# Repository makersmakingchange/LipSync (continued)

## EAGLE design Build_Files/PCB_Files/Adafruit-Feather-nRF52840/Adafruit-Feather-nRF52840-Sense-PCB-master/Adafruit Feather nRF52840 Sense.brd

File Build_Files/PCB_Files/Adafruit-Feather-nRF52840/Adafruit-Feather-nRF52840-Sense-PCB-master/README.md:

## Adafruit Feather nRF52840 Sense PCB

<a href="http://www.adafruit.com/products/4516"><br/>
Click here to purchase one from the Adafruit shop</a>

PCB files for the Adafruit Feather nRF52840 Sense. 

Format is EagleCAD schematic and board layout
* https://www.adafruit.com/product/4516

### Description

The Adafruit Feather Bluefruit Sense takes our popular Feather nRF52840 Express and adds a smorgasbord of sensors to make a great wireless sensor platform. This Feather microcontroller comes with Bluetooth Low Energy and native USB support featuring the nRF52840!  This Feather is an 'all-in-one' Arduino-compatible + Bluetooth Low Energy with built in USB plus battery charging. With native USB it works great with CircuitPython, too.

Like the Feather nRF52840, this chip comes with Arduino IDE support - you can program the nRF52840 chip directly to take full advantage of the Cortex-M4 processor, and then calling into the Nordic SoftDevice radio stack when you need to communicate over BLE. Since the underlying API and peripherals are the same for the '832 and '840, you can supercharge your older nRF52832 projects with the same exact code, with a single recompile!

This Feather is also a BLE-friendly CircuitPython board! CircuitPython works best with disk drive access, and this is the only BLE-plus-USB-native chip that has the memory to handle running a little Python interpreter. The massive RAM and speedy Cortex M4F chip make this a good match. Make centrals or peripherals with the ease of CircuitPython.

A chorus of supporting sensors surround the module so you can do all sorts of environmental and motion sensing:

* ST Micro series 9-DoF motion - LSM6DS33 Accel/Gyro + LIS3MDL magnetometer
* APDS9960 Proximity, Light, Color, and Gesture Sensor
* PDM Microphone sound sensor
* SHT Humidity
* BMP280 temperature and barometric pressure/altitude

Features:

* ARM Cortex M4F (with HW floating point acceleration) running at 64MHz
* 1MB flash and 256KB SRAM
* Native Open Source USB stack - pre-programmed with UF2 bootloader
* Bluetooth Low Energy compatible 2.4GHz radio (Details available in the nRF52840 product specification)
* FCC / IC / TELEC certified module
* Up to +8dBm output power
* 21 GPIO, 6 x 12-bit ADC pins, up to 12 PWM outputs (3 PWM modules with 4 outputs each)
* Pin #13 red LED for general purpose blinking, Blue LED for general purpose connection status, NeoPixel for colorful feedback
* Power/enable pin
* Measures 2.0" x 0.9" x 0.28" (51mm x 23mm x 7.2mm) without headers soldered in
* Light as a (large?) feather - 6 grams
* 4 mounting holes
* Reset button
* SWD debug pads on bottom of PCB
* Works out of the box with all of our Adafruit FeatherWings! (Even the UART-using ones like the GPS FeatherWing)

### License

Adafruit invests time and resources providing this open source design, please support Adafruit and open-source hardware by purchasing products from [Adafruit](https://www.adafruit.com)!

Designed by Limor Fried/Ladyada for Adafruit Industries.

Creative Commons Attribution/Share-Alike, all text above must be included in any redistribution. 
See license.txt for additional details.

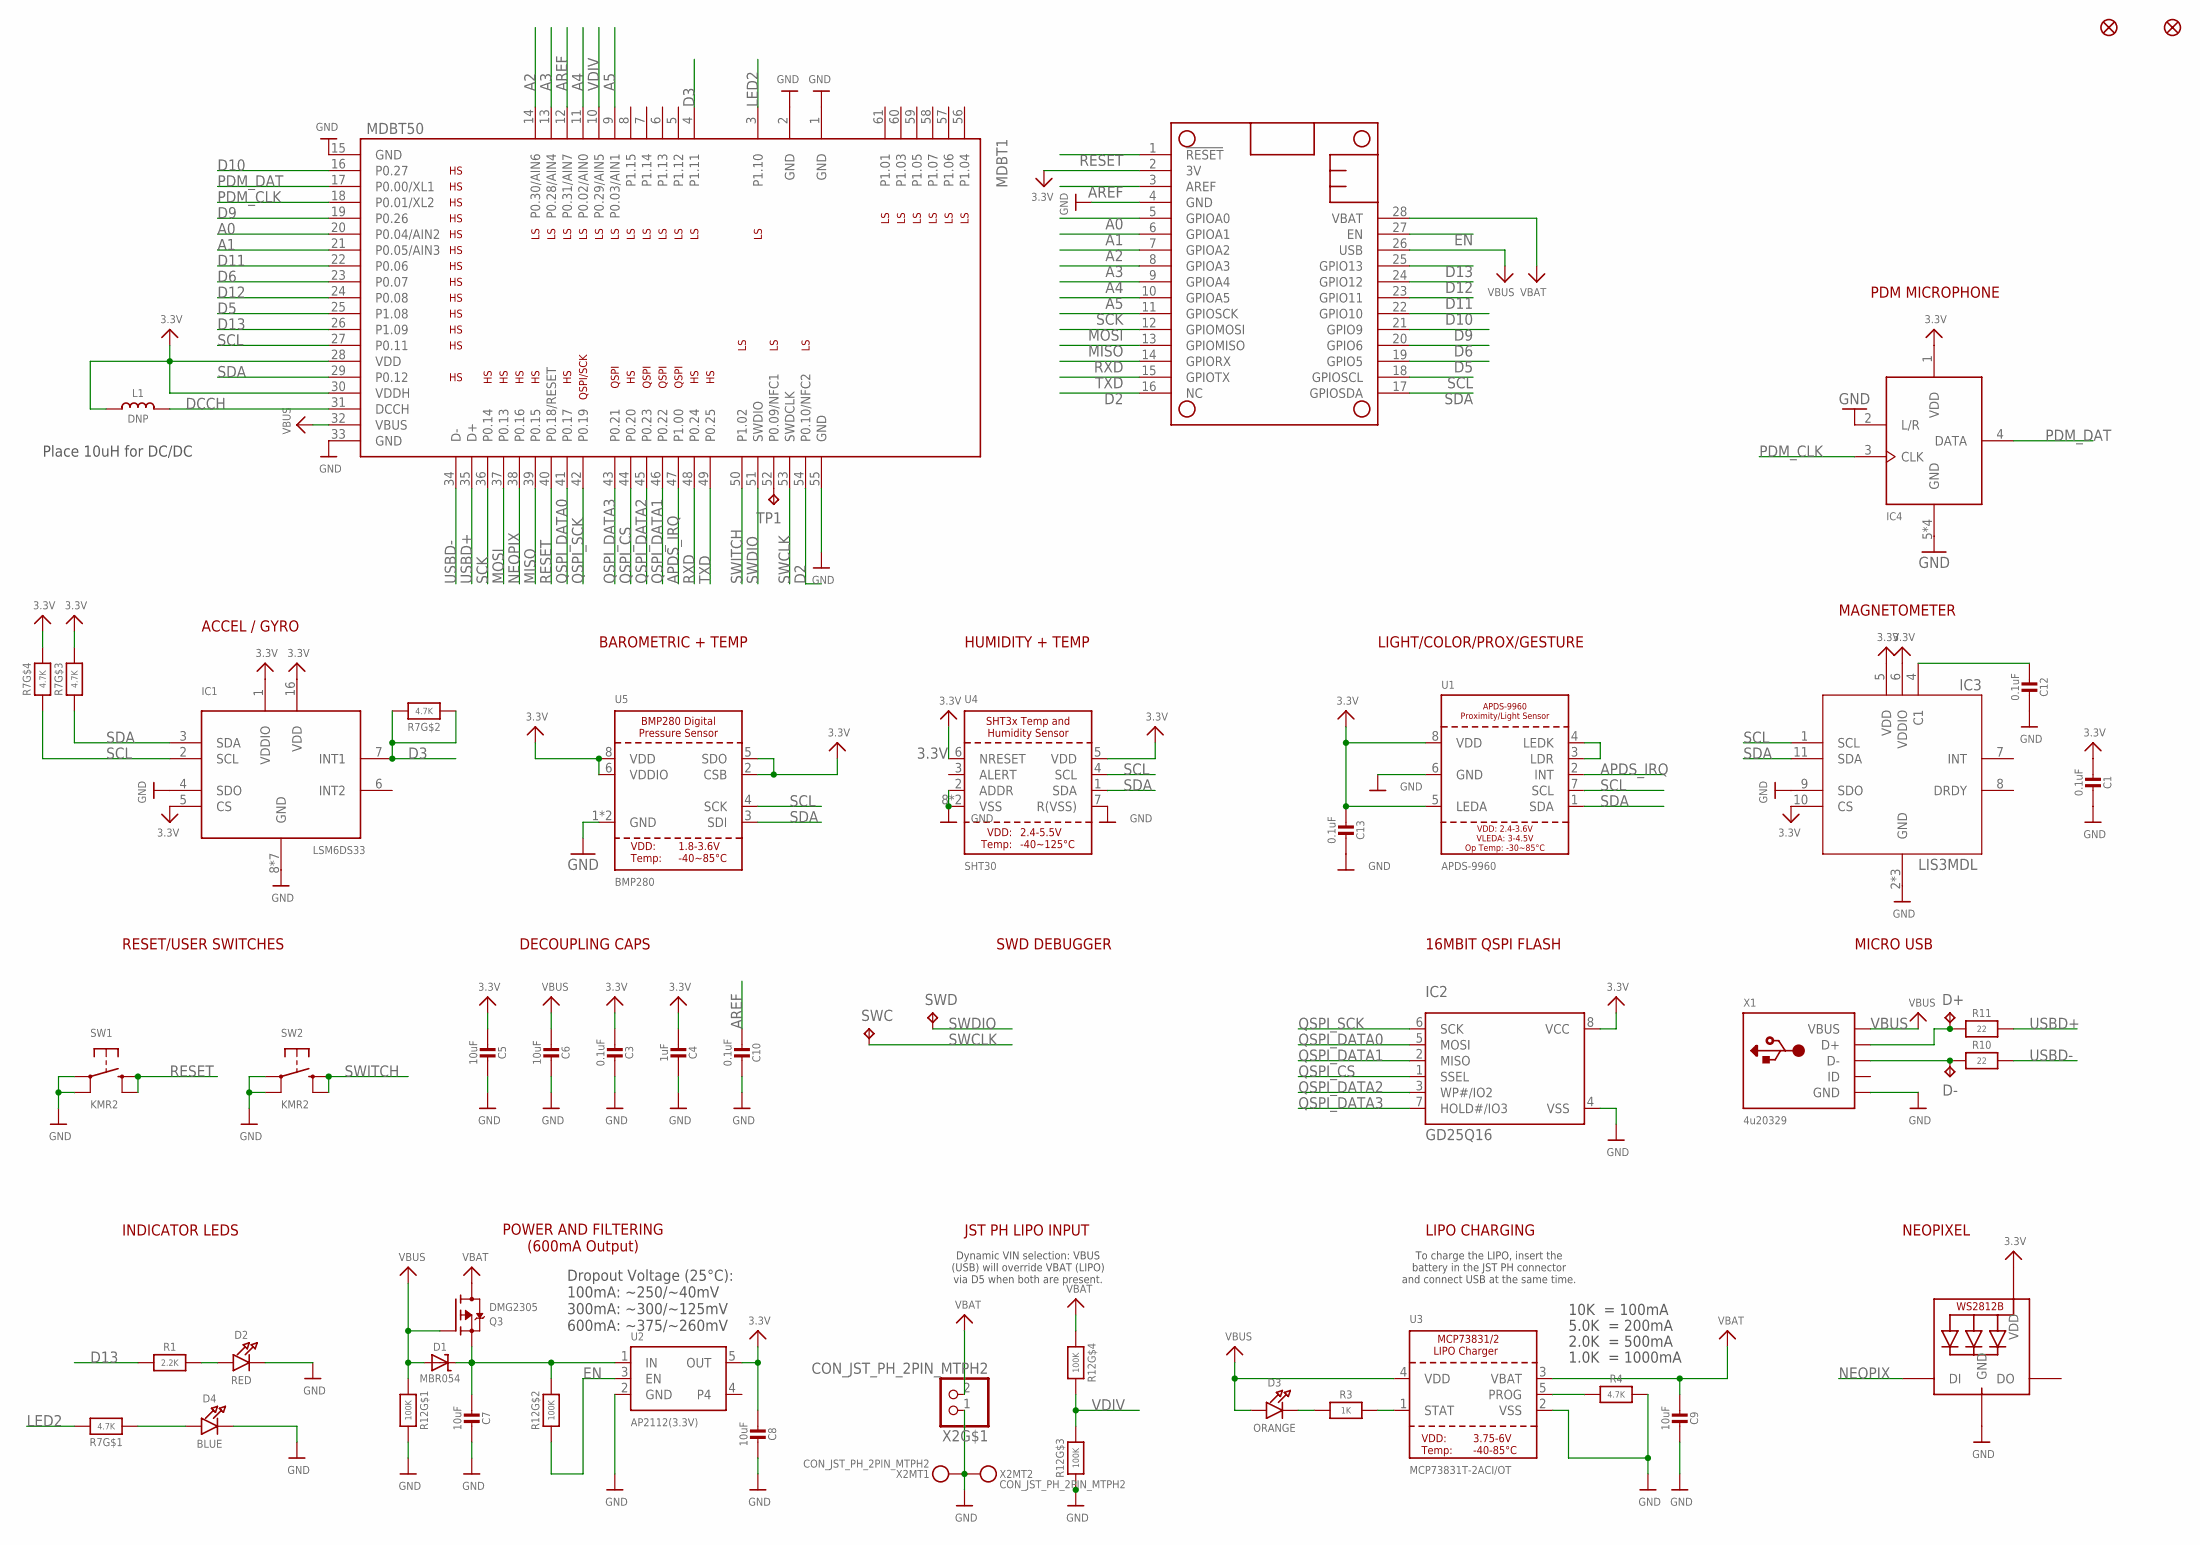
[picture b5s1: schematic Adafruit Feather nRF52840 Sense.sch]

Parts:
C1, C3, C10, C12, C13: 0.1uF; 0603-NO
C4: 1uF; 0603-NO
C5, C6, C7, C8, C9: 10uF; 0805-NO
D1: MBR054; SOD-123
D2: RED; CHIPLED_0805_NOOUTLINE
D3: ORANGE; CHIPLED_0805_NOOUTLINE
D4: BLUE; CHIPLED_0603_NOOUTLINE
D+: TPTP10R; TP10R
D-: TPTP10R; TP10R
FID1, FID2: FIDUCIAL_1MM
IC1: LSM6DS33; LGA16_3X3MM
IC2: GD25Q16; USON8
IC3: LIS3MDL; LGA12_2X2MM
IC4: MIC_PDM; SPK0415HM4H
L1: DNP; _0805MP
LED1: WS2812B3535; LED3535
MDBT1: MDBT50
MS1: FEATHERWING_NODIM
Q3: DMG2305; SOT23-R
R1: 2.2K; 0603-NO
R3: 1K; 0603-NO
R4: 4.7K; 0603-NO
R7: 4.7K; RESPACK_4X0603
R10, R11: 22; 0603-NO
R12: 100K; RESPACK_4X0603
SW1, SW2: KMR2; BTN_KMR2_4.6X2.8
SWC: TPTP12R; TP12R
SWD: TPTP12R; TP12R
TP1: TPTP10R; TP10R
U1: APDS-9960
U2: AP2112(3.3V); SOT23-5
U3: MCP73831T-2ACI/OT; SOT23-5
U4: SHT30; SHT3X
U5: BMP280
X1: 4u20329; 4UCONN_20329_V2
X2: CON_JST_PH_2PIN_MTPH2; JSTPH2

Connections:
3.3V: C1.2, C3.2, C4.2, C5.2, C8.2, C13.2, IC1.1 (VDDIO), IC1.5 (CS), IC1.16 (VDD), IC2.8 (VCC), IC3.5 (VDD), IC3.6 (VDDIO), IC3.10 (CS), IC4.1 (VDD), L1.1, LED1.2 (VDD), MDBT1.28 (VDD), MDBT1.30 (VDDH), MS1.2 (3V), R7.5 (2), R7.6 (2), U1.5 (LEDA), U1.8 (VDD), U2.5 (OUT), U4.5 (VDD), U4.6 (NRESET), U5.2 (CSB), U5.5 (SDO), U5.6 (VDDIO), U5.8 (VDD)
A0: MDBT1.20 (P0.04/AIN2), MS1.5 (GPIOA0)
A1: MDBT1.21 (P0.05/AIN3), MS1.6 (GPIOA1)
A2: MDBT1.14 (P0.30/AIN6), MS1.7 (GPIOA2)
A3: MDBT1.13 (P0.28/AIN4), MS1.8 (GPIOA3)
A4: MDBT1.11 (P0.02/AIN0), MS1.9 (GPIOA4)
A5: MDBT1.9 (P0.03/AIN1), MS1.10 (GPIOA5)
APDS_IRQ: MDBT1.47 (P1.00), U1.2 (INT)
AREF: C10.2, MDBT1.12 (P0.31/AIN7), MS1.3 (AREF)
CAP1: C12.2, IC3.4 (C1)
D2: MDBT1.54 (P0.10/NFC2), MS1.16 (NC)
D3: IC1.7 (INT1), MDBT1.4 (P1.11), R7.2 (1), R7.7 (2)
D5: MDBT1.25 (P1.08), MS1.19 (GPIO5)
D6: MDBT1.23 (P0.07), MS1.20 (GPIO6)
D9: MDBT1.19 (P0.26), MS1.21 (GPIO9)
D10: MDBT1.16 (P0.27), MS1.22 (GPIO10)
D11: MDBT1.22 (P0.06), MS1.23 (GPIO11)
D12: MDBT1.24 (P0.08), MS1.24 (GPIO12)
D13: MDBT1.26 (P1.09), MS1.25 (GPIO13), R1.1
D+: D+.TP, R11.1, X1.D+
D-: D-.TP, R10.1, X1.D-
DCCH: L1.2, MDBT1.31 (DCCH)
EN: MS1.27 (EN), R12.2 (1), U2.3 (EN)
GND: C1.1, C3.1, C4.1, C5.1, C6.1, C7.1, C8.1, C9.1, C10.1, C12.1, C13.1, D2.C, D4.C, IC1.4 (SDO), IC1.8 (GND), IC1.9 (GND), IC1.10 (GND), IC1.11 (GND), IC1.12 (GND), IC1.13 (GND), IC1.15 (GND), IC2.4 (VSS), IC3.2 (GND), IC3.3 (GND), IC3.9 (SDO), IC3.12 (GND), IC4.2 (L/R), IC4.5 (GND), IC4.6 (GND), IC4.7 (GND), IC4.8 (GND), LED1.4 (GND), MDBT1.1 (GND), MDBT1.2 (GND), MDBT1.15 (GND), MDBT1.33 (GND), MDBT1.55 (GND), MS1.4 (GND), R4.2, R12.3 (1), R12.8 (2), SW1.A, SW1.A' (P1), SW2.A, SW2.A' (P1), U1.6 (GND), U2.2 (GND), U3.2 (VSS), U4.2 (ADDR), U4.7 (R(VSS)), U4.8 (VSS), U4.THERMAL (VSS), U5.1 (GND), U5.7 (GND), X1.BASE@1 (GND), X1.BASE@2 (GND), X1.GND, X1.SPRT@1 (GND), X1.SPRT@2 (GND), X1.SPRT@3 (GND), X1.SPRT@4 (GND), X2.1, X2.NC1, X2.NC2
LED2: MDBT1.3 (P1.10), R7.8 (2)
MISO: MDBT1.39 (P0.15), MS1.13 (GPIOMISO)
MOSI: MDBT1.37 (P0.13), MS1.12 (GPIOMOSI)
unnamed: D3.C, R3.1
unnamed: U1.3 (LDR), U1.4 (LEDK)
unnamed: D4.A, R7.1
unnamed: D2.A, R1.2
unnamed: R3.2, U3.1 (STAT)
unnamed: R4.1, U3.5 (PROG)
NEOPIX: LED1.1 (DI), MDBT1.38 (P0.16)
NFC2: MDBT1.52 (P0.09/NFC1), TP1.TP
PDM_CLK: IC4.3 (CLK), MDBT1.18 (P0.01/XL2)
PDM_DAT: IC4.4 (DATA), MDBT1.17 (P0.00/XL1)
QSPI_CS: IC2.1 (SSEL), MDBT1.44 (P0.20)
QSPI_DATA0: IC2.5 (MOSI), MDBT1.41 (P0.17)
QSPI_DATA1: IC2.2 (MISO), MDBT1.46 (P0.22)
QSPI_DATA2: IC2.3 (WP#/IO2), MDBT1.45 (P0.23)
QSPI_DATA3: IC2.7 (HOLD#/IO3), MDBT1.43 (P0.21)
QSPI_SCK: IC2.6 (SCK), MDBT1.42 (P0.19)
RESET: MDBT1.40 (P0.18/RESET), MS1.1 (!RESET), SW1.B (S), SW1.B' (S1)
RXD: MDBT1.48 (P0.24), MS1.14 (GPIORX)
SCK: MDBT1.36 (P0.14), MS1.11 (GPIOSCK)
SCL: IC1.2 (SCL), IC3.1 (SCL), MDBT1.27 (P0.11), MS1.18 (GPIOSCL), R7.4 (1), U1.7 (SCL), U4.4 (SCL), U5.4 (SCK)
SDA: IC1.3 (SDA), IC3.11 (SDA), MDBT1.29 (P0.12), MS1.17 (GPIOSDA), R7.3 (1), U1.1 (SDA), U4.1 (SDA), U5.3 (SDI)
SWCLK: MDBT1.53 (SWDCLK), SWC.TP
SWDIO: MDBT1.51 (SWDIO), SWD.TP
SWITCH: MDBT1.50 (P1.02), SW2.B (S), SW2.B' (S1)
TXD: MDBT1.49 (P0.25), MS1.15 (GPIOTX)
USBD+: MDBT1.35 (D+), R11.2
USBD-: MDBT1.34 (D-), R10.2
VBAT: C9.2, MS1.28 (VBAT), Q3.3 (D), R12.4 (1), U3.3 (VBAT), X2.2
VBUS: C6.2, D1.A, D3.A, MDBT1.32 (VBUS), MS1.26 (USB), Q3.1 (G), R12.1, U3.4 (VDD), X1.VBUS
VDIV: MDBT1.10 (P0.29/AIN5), R12.5 (2), R12.6 (2)
VHI: C7.2, D1.C, Q3.2 (S), R12.7 (2), U2.1 (IN)

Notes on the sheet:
10K = 100mA
5.0K = 200mA
2.0K = 500mA
1.0K = 1000mA
LIPO CHARGING
To charge the LIPO, insert the battery in the JST PH connector and connect USB at the same time.
POWER AND FILTERING (600mA Output)
JST PH LIPO INPUT
Dynamic VIN selection: VBUS (USB) will override VBAT (LIPO) via D5 when both are present.
Dropout Voltage (25°C): 100mA: ~250/~40mV 300mA: ~300/~125mV 600mA: ~375/~260mV
INDICATOR LEDS
RESET/USER SWITCHES
DECOUPLING CAPS
SWD DEBUGGER
16MBIT QSPI FLASH
MICRO USB
NEOPIXEL
Place 10uH for DC/DC
ACCEL / GYRO
BAROMETRIC + TEMP
HUMIDITY + TEMP
LIGHT/COLOR/PROX/GESTURE
MAGNETOMETER
PDM MICROPHONE

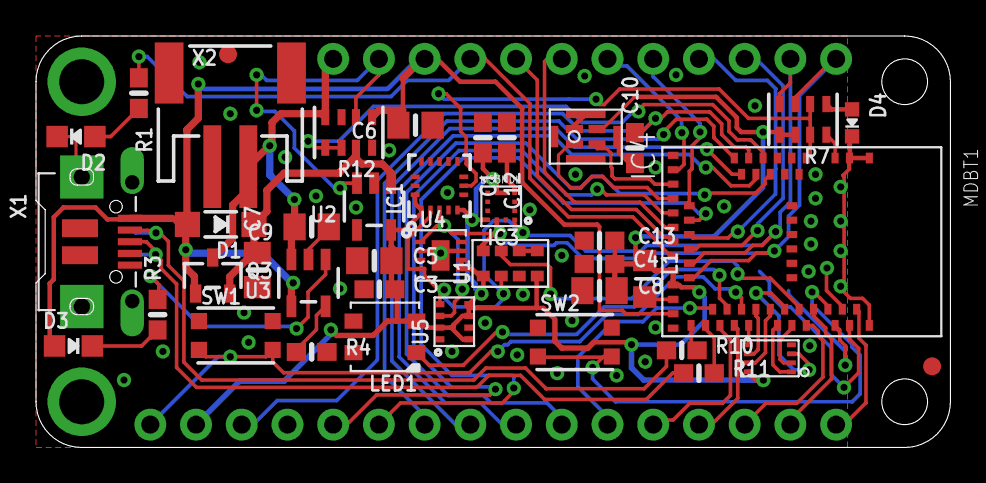
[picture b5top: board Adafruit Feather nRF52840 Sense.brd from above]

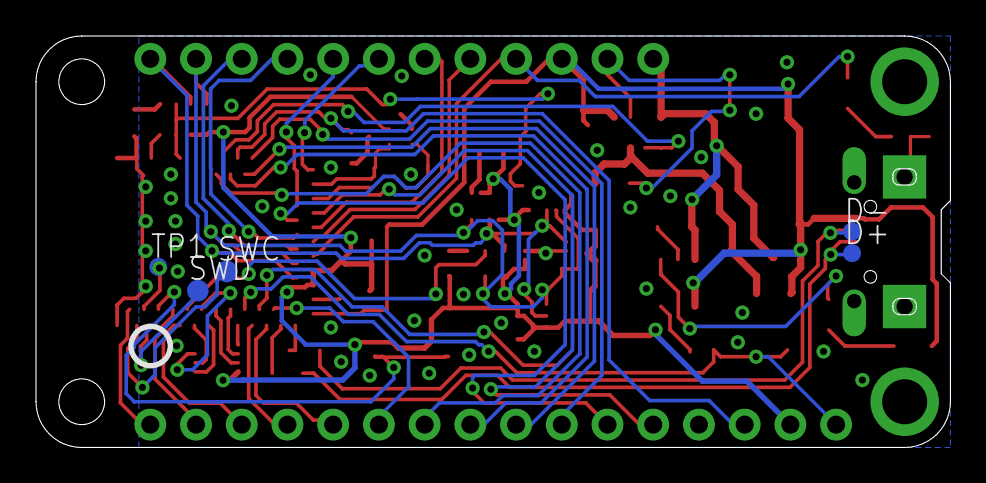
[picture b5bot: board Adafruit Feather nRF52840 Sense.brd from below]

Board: 4 copper layers, 50.8 x 22.9 mm, 50 parts (7 on the bottom side), 58 nets.

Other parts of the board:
U$10: PCBFEAT-REV-056
U$14: FEATHERSENSE_TOP
U$75: FEATHERSENSE_BOT

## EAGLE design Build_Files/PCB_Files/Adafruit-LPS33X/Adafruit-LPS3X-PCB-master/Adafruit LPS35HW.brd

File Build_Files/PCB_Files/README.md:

# LipSync 4.0 PCB Files

PCB files for the LipSync 4.0.

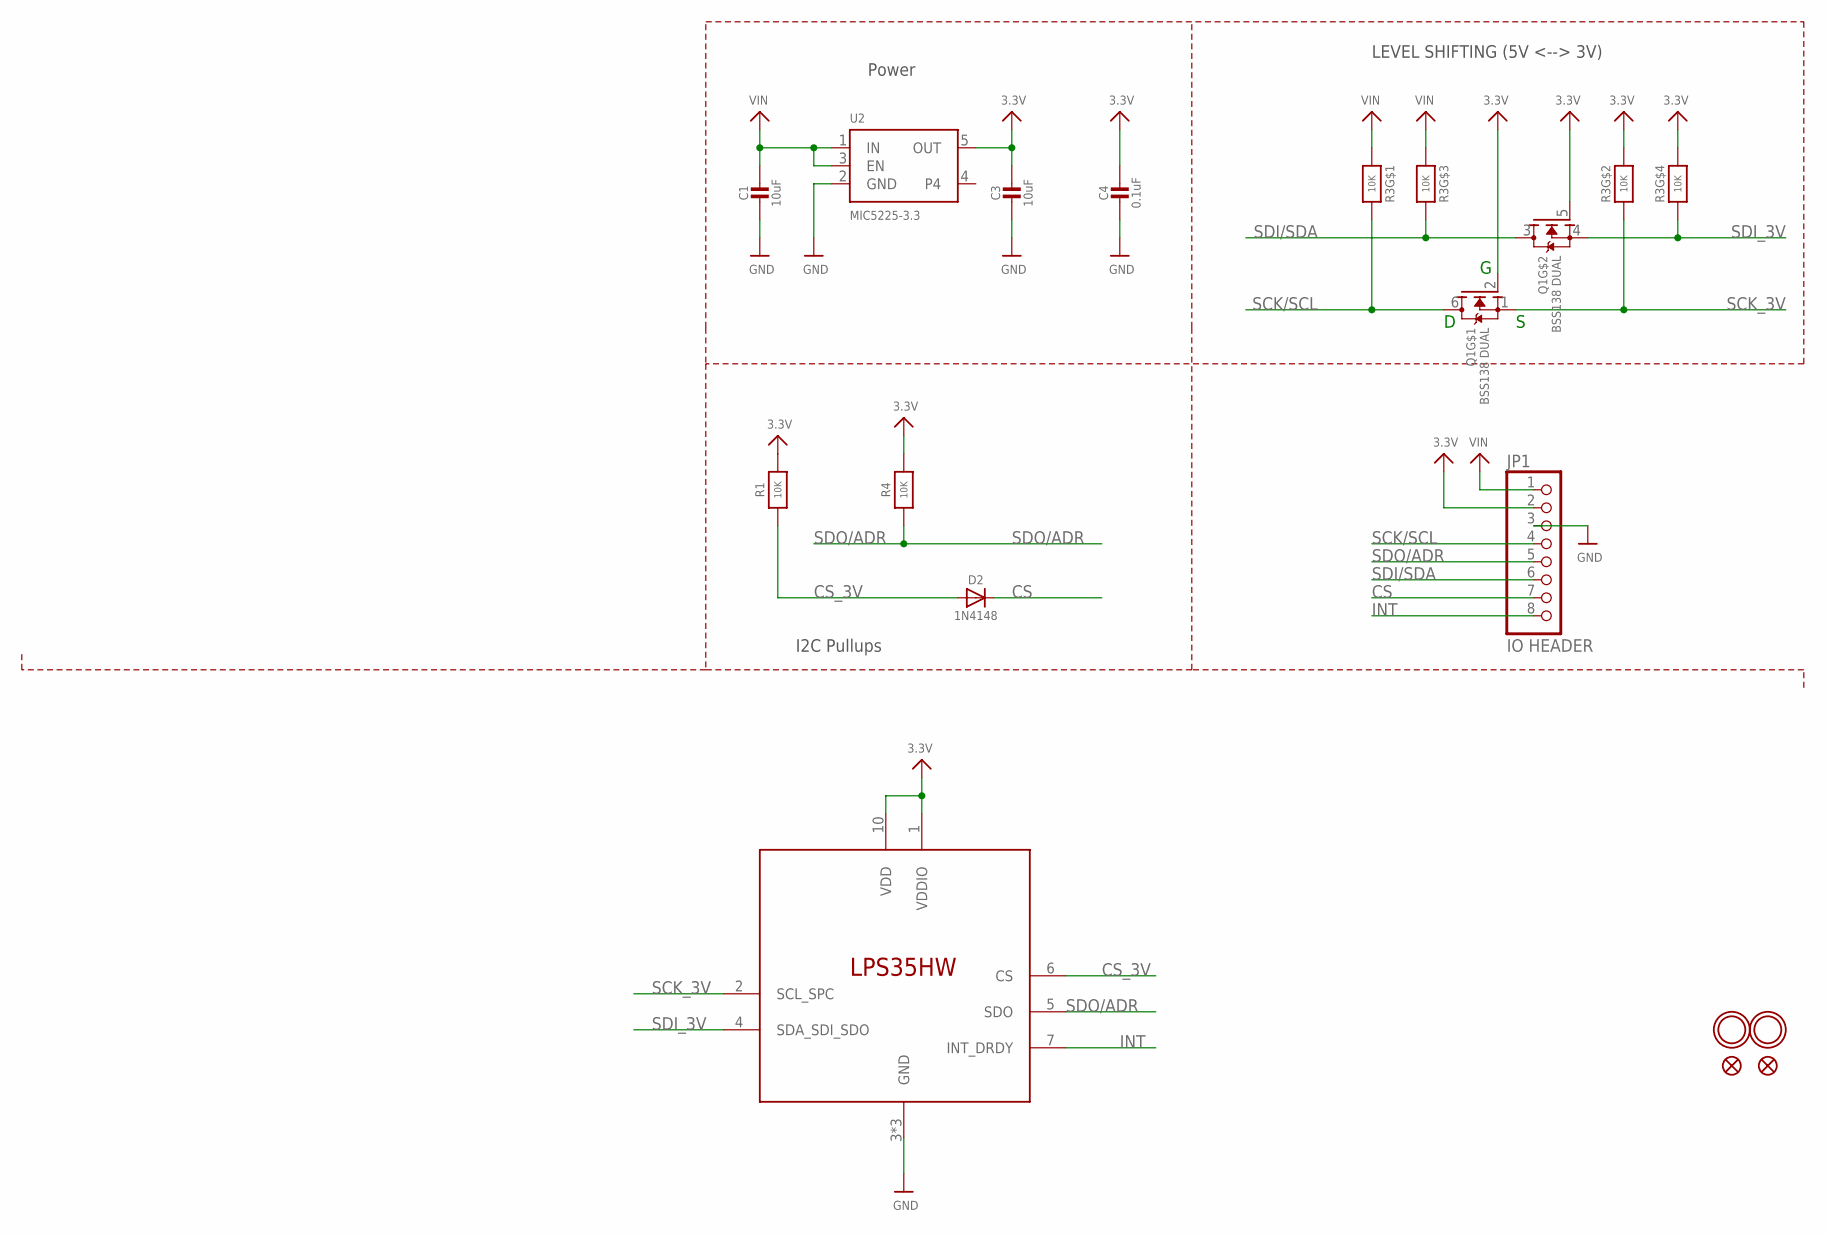
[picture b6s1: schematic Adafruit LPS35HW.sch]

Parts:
C1, C3: 10uF; 0805-NO
C4: 0.1uF; 0603-NO
D2: 1N4148; SOD-323
JP1: IO HEADER; 1X08_ROUND
Q1: BSS138 DUAL; SOT363
R1, R4: 10K; 0603-NO
R3: 10K; RESPACK_4X0603
U2: MIC5225-3.3; SOT23-5
U$3: LPS35HWLPS35HW; CCLGA10L
U$5, U$15: FIDUCIAL_1MM
U$7, U$8: MOUNTINGHOLE2.0; MOUNTINGHOLE_2.0_PLATED

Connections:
3.3V: C3.1, C4.1, JP1.2, Q1.2 (G), Q1.5 (G), R1.2, R3.2 (1), R3.4 (1), R4.2, U2.5 (OUT), U$3.1 (VDDIO), U$3.10 (VDD)
CS: D2.C, JP1.7
CS_3V: D2.A, R1.1, U$3.6 (CS)
GND: C1.2, C3.2, C4.2, JP1.3, U2.2 (GND), U$3.3 (GND), U$3.8 (GND), U$3.9 (GND)
INT: JP1.8, U$3.7 (INT_DRDY)
SCK/SCL: JP1.4, Q1.6 (D), R3.8 (2)
SCK_3V: Q1.1 (S), R3.7 (2), U$3.2 (SCL_SPC)
SDI/SDA: JP1.6, Q1.3 (D), R3.6 (2)
SDI_3V: Q1.4 (S), R3.5 (2), U$3.4 (SDA_SDI_SDO)
SDO/ADR: JP1.5, R4.1, U$3.5 (SDO)
VIN: C1.1, JP1.1, R3.1, R3.3 (1), U2.1 (IN), U2.3 (EN)

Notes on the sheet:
LEVEL SHIFTING (5V <--> 3V)
I2C Pullups
Power

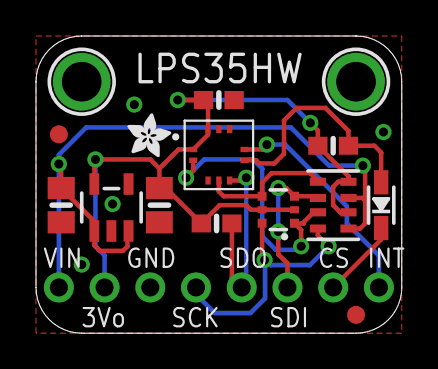
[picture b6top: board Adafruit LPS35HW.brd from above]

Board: 2 copper layers, 20.3 x 16.5 mm, 17 parts (1 on the bottom side), 11 nets.

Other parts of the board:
U$2, U$6: ADAFRUIT_2.5MM

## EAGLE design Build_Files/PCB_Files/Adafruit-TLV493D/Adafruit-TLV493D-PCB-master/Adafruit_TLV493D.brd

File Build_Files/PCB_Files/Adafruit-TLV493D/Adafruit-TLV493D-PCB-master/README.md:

## Adafruit TLV493D Triple-Axis Magnetometer PCB

<a href="http://www.adafruit.com/products/4366"><br/>
Click here to purchase one from the Adafruit shop</a>

PCB files for the Adafruit TLV493D Triple-Axis Magnetometer. 

Format is EagleCAD schematic and board layout
* https://www.adafruit.com/product/4366

### Description
The TLV493D 3-axis magnetometer is a great little sensor for detecting magnets [_in 3D_](https://www.youtube.com/watch?v=3FQDUX6X6-w). In fact, the manufacturer Infineon suggests it could be used to make a joystick! You could also use it for other cool things like detecting objects with magnets attached, like the lid of a box, or maybe a statue that unlocks your secret lair when placed on your mantle?

The TLD493D excels at measuring nearby magnetic fields in three dimensions. It's not going to make a good compass, it's not sensitive enough to pick up the Earth's magnetic field, but you can use it to track the movement of nearby magnets in three dimensions. 

Here are a few specs:

 * Digital output via 2-wire based standard I2C interface up to 1 MBit/sec
 * 12-bit data resolution for each measurement direction
 * Bx, By and Bz linear field measurement up to +130 [mT](https://en.wikipedia.org/wiki/Tesla_\(unit\))
 * Excellent matching of X/Y measurement for accurate angle sensing

As we are wont to do, we've made the TLV easy to use by putting it on a breakout PCB along with the circuitry to support it. A voltage regulator and logic level shifting combine to make it usable with a range of microcontrollers with either 3.3V or 5V logic levels. We even give you a pin for you to use the excess 3.3V juice not needed by the TLV493D.

We've also outfitted the breakout with [SparkFun Qwiic](https://www.sparkfun.com/qwiic) compatible [STEMMA QT](https://learn.adafruit.com/introducing-adafruit-stemma-qt) connectors to allow you to use it with other similarly equipped boards without needing to solder. Because the TLV493D "speaks" I2C, you only need two wires (in addition to power) to interface with your microcontroller, and you can share those pins with other I2C sensors. The manufacturer Infineon was kind enough to provide a library to use the sensor with Arduino, and we've written one to use it with CircuitPython and Python for use on Raspberry Pi and other Linux computers.

### License

Adafruit invests time and resources providing this open source design, please support Adafruit and open-source hardware by purchasing products from [Adafruit](https://www.adafruit.com)!

Designed by Kattni Rembor for Adafruit Industries.

Creative Commons Attribution/Share-Alike, all text above must be included in any redistribution. 
See license.txt for additional details.

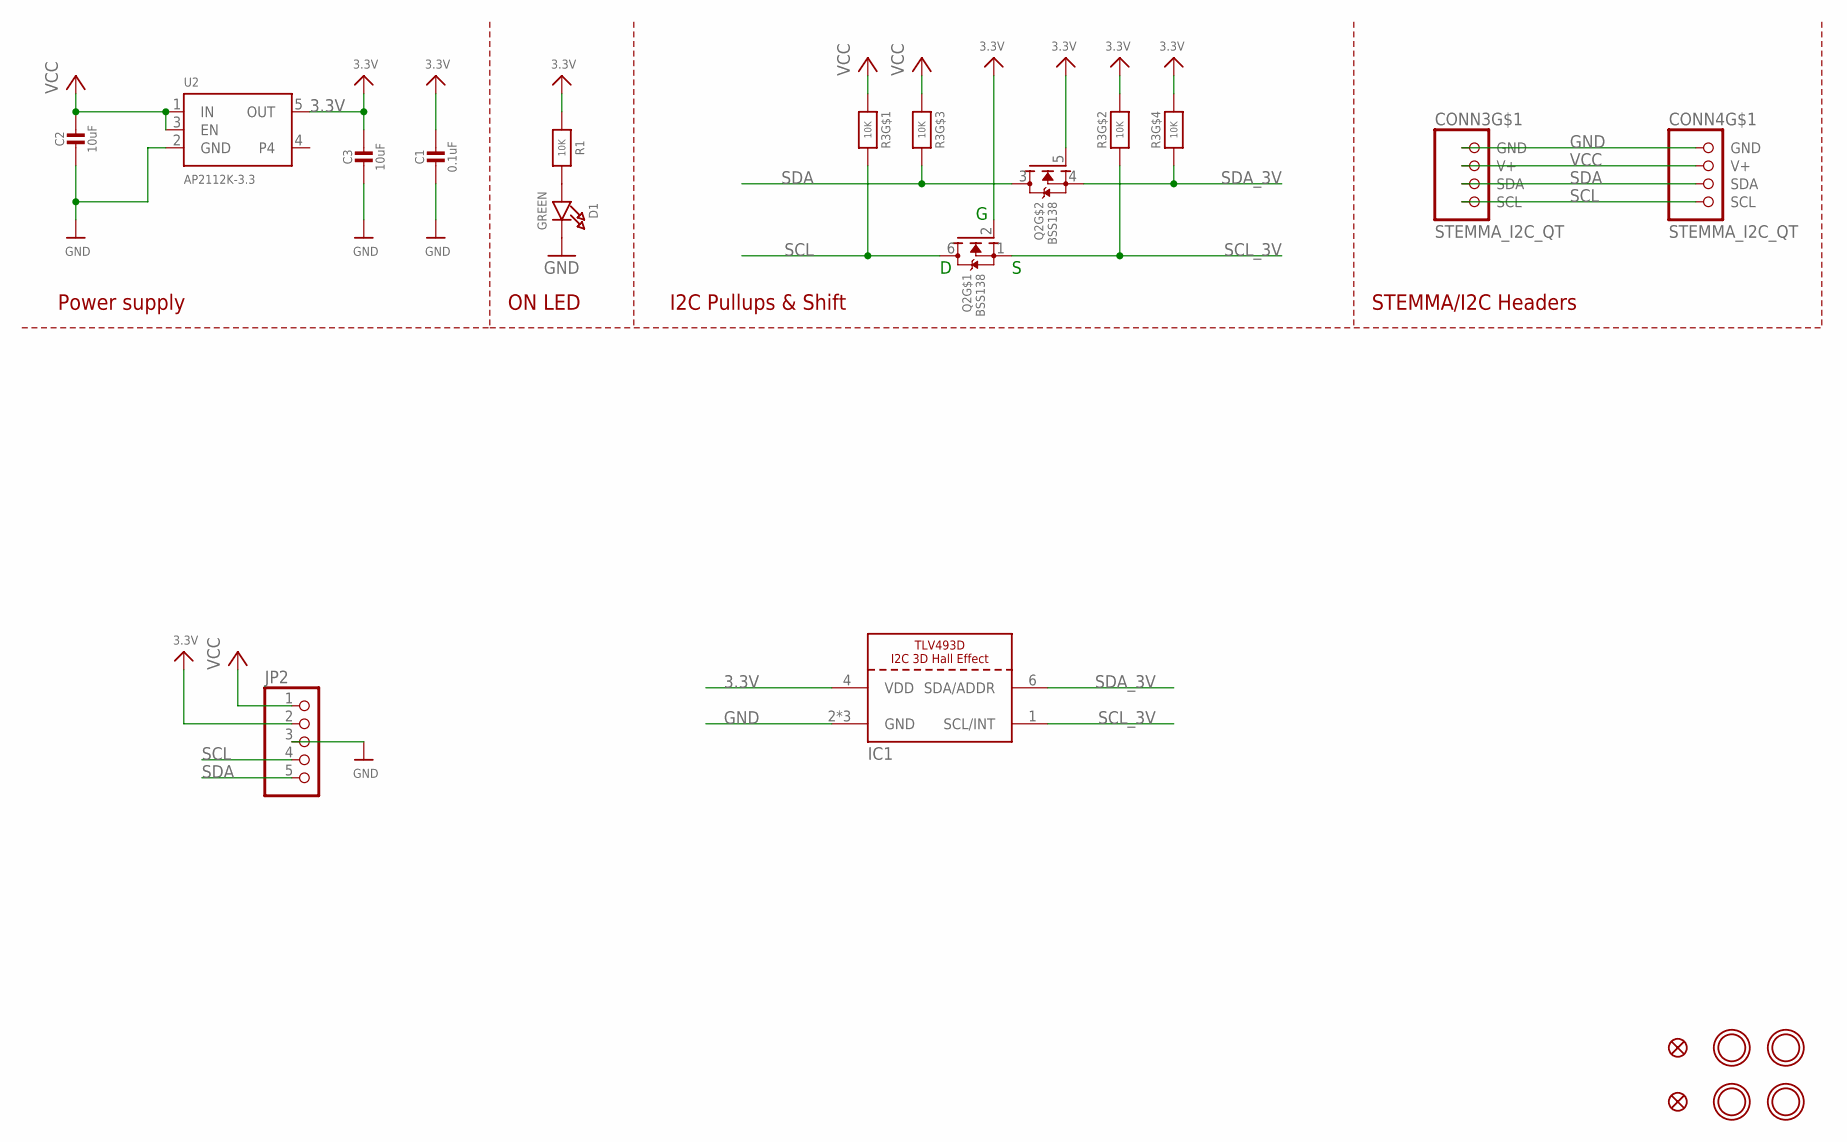
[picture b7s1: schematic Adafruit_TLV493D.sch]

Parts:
C1: 0.1uF; 0603-NO
C2, C3: 10uF; 0805-NO
CONN3, CONN4: STEMMA_I2C_QT; JST_SH4
D1: GREEN; CHIPLED_0603_NOOUTLINE
FID3, FID4: FIDUCIAL_1MM
IC1: TLV493D; SOT23-6
JP2: HEADER-1X5ROUND; 1X05_ROUND
Q2: BSS138; SOT363
R1: 10K; 0603-NO
R3: 10K; RESPACK_4X0603
U2: AP2112K-3.3; SOT23-5
U$1, U$17, U$19, U$21: MOUNTINGHOLE2.5; MOUNTINGHOLE_2.5_PLATED

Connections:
3.3V: C1.1, C3.1, IC1.4 (VDD), JP2.2, Q2.2 (G), Q2.5 (G), R1.1, R3.2 (1), R3.4 (1), U2.5 (OUT)
GND: C1.2, C2.2, C3.2, CONN3.1 (GND), CONN4.1 (GND), D1.C, IC1.2 (GND), IC1.3 (GND), IC1.5 (GND), JP2.3, U2.2 (GND)
unnamed: D1.A, R1.2
SCL: CONN3.4 (SCL), CONN4.4 (SCL), JP2.4, Q2.6 (D), R3.8 (2)
SCL_3V: IC1.1 (SCL/INT), Q2.1 (S), R3.7 (2)
SDA: CONN3.3 (SDA), CONN4.3 (SDA), JP2.5, Q2.3 (D), R3.6 (2)
SDA_3V: IC1.6 (SDA/ADDR), Q2.4 (S), R3.5 (2)
VCC: C2.1, CONN3.2 (V+), CONN4.2 (V+), JP2.1, R3.1, R3.3 (1), U2.1 (IN), U2.3 (EN)

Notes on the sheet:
I2C Pullups & Shift
STEMMA/I2C Headers
ON LED
Power supply

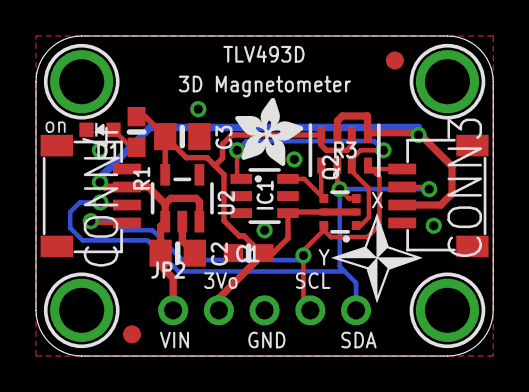
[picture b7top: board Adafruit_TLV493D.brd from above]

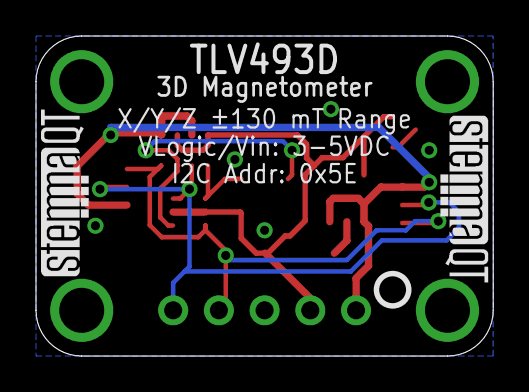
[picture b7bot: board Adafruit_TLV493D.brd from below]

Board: 2 copper layers, 25.4 x 17.8 mm, 24 parts (4 on the bottom side), 8 nets.

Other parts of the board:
U$2: SYMBOL_COMPASSXY_5MM
U$4: KATTNI_STOP
U$22: ADAFRUIT_3.5MM
U$25: PCBFEAT-REV-040
U$30, U$31: STEMMAQT

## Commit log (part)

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2024-01-23 Squashed commit of the following:
    commit 491d6348e13f18c0dd77c227a2045bb1d19f8777
    Author: jversloot <50920198+jversloot@users.noreply.github.com>
    Date: Tue Jan 23 16:37:36 2024 -0400
    Updated function names
    Renamed Joystick Speed to Cursor Speed in various functions and variables
    commit 89f2f2929f992e014305fbac422cc0d2adc24e7e
2024-01-24 Added full calibration prompts
2024-01-24 Center reset now triggers startup noise and Center Reset Complete page
2024-01-24 Added screen prompts to center reset when activated from Sw2
2024-01-24 Updated default values for full extents to match current design
2024-01-24 Squashed commit of the following:
    commit 54c3aa7eed507ad014a13c1c80f4aa6799c7f14b
    Author: jversloot <50920198+jversloot@users.noreply.github.com>
    Date: Wed Jan 24 18:10:52 2024 -0400
    Updated default values for full extents to match current design
    commit aae6c582d858a4612ec0af446fea291cca5a156d
    Author: jversloot <50920198+jversloot@users.noreply.github.com>
2024-01-24 Update LSOutput.h
    Simplify / reduce colors
2024-01-25 Move mapping to LSConfig.h
    Moved ledActionProperty, switchActionProperty, buttonActionProperty, and sapActionProperty to LSConfig.h
2024-01-25 Updated splash screens
2024-01-25 Update LSConfig.h
    Default light setup
2024-01-25 Fixed bug in mode menu
    Fixed bug where current mode would become un-highlighted if you circled through the menu
2024-01-25 Cleaned up repeated variable and changed Bluetooth device name
2024-01-25 Initial Light Mode Implementation
    Added globals, APIs, and functions in LSOutput.h
2024-01-25 Cleanup
2024-01-25 Update LSScreen.h
    Item typo and caps
2024-01-25 Update LipSync_Firmware.ino
    Cleanup
2024-01-26 Match timing to LipSync original
    1000 / 3000 / 5000 instead of 3000 / 5000
2024-01-26 Updated input/output mapping
2024-01-26 Renamed testing code files
2024-01-31 Changed gamepad lights mapping
2024-02-03 Add V4.0 print files
2024-02-03 Add V4.0 PCB Build files
2024-02-03 Add v4.0 PCB files
2024-02-03 Remove 3rd party PCB files
2024-02-06 Update User Guide formatting
2024-02-10 Add Open Source Hardware Certification
    Add Open Source Hardware information to readme and PCB
    Add license graphic
    Update PCB Build Files
2024-02-21 Update LS4_Hub_Top.stl
    Fix print orientation
2024-02-28 Fixed typo in User Guide
2024-03-11 added print statements to performJoystickCenter
2024-03-12 Fixed sip and puff threshold memory
2024-04-05 Added the Modular Mounting System
    Added the documentation, design, and build files for the LipSync Hub Modular Mounting System. Added a reference to the LHMMS in the maker guide so that the maker knows that it is an option
2024-04-23 V4.0.1 - Bug Fix for Tiny USB Library version
2024-04-24 Update LSConfig.h
    -renumber CONF_ACTIONS to fix LED mapping
2024-04-24 Update LSConfig.h
    Fix up LED action mapping
2024-04-25 Added timeout message
    Added message before changing mode and resetting
2024-04-25 Fixed colours of onboard LED for operating mode
2024-04-29 Fixed default lights after drag or scroll
2024-05-01 Update LSAPI.ino
    Fix unused variable / compiler error.
2024-05-01 Update LSMemory.h
    Update ArduinoJson for now obsolete createdNestedArray()
    https://arduinojson.org/v7/how-to/upgrade-from-v6/
2024-05-02 Updated library version in Maker Guide
2024-08-23 Fixed typo in ReadMe
2024-10-17 Added video build guide
    Added link to the youtube video build guide
2024-11-28 Commented out additional debugging lines
2024-12-05 Update LSPressure.h
    improve readability
2024-12-16 Moved full calibration to More menu and added confirmation screen
2025-01-09 Update LSScreen.h
    Change _maxCharPerLine to unsigned int to remove compiler warning.
2025-01-10 Update LSJoystick.h
    Begin swap to new TLx493D library
2025-01-13 Add sensor i2c addresses
2025-01-16 Remove infinite loops and replaced with hardcoded timeouts
2025-01-17 Removed USB timeout code that auto switches to BT mouse.
2025-01-17 Added error message on display for no USB
2025-01-20 Changed so error message only appears when trying to connect to USB
2025-01-21 Update LSConfig.h
    Remove LED_STATE_OFF and LED_STATE_ON to avoid compiler error
2025-01-21 Update copyright and version
2025-01-21 Update LSUSB.h
    Change type of usbTimeoutMillis from int to unsigned long to match millis() type
2025-01-21 Update LipSync_Firmware.ino
    Initialize tempDefaultPoint to remove compiler error
2025-01-21 Fixed error in USB timeout timers and fixed XAC connection bug
2025-01-21 Update LipSync_Firmware.ino
    Added comments for function descriptions
2025-01-23 Update LSConfig.h
    Add additional error codes
2025-01-24 Update LipSync_Firmware.ino
    Comments for future cleanup
2025-01-24 Update buzzer
    Add comments, and proper order to class, create better function names, add error sound, add ready to use sound, add buzzer test.
2025-01-25 Change startup sound
2025-01-25 Update LSTest.ino
    Add LED brightness test
2025-01-25 Update LipSync_Firmware.ino
    Change errorCode to g_errorCode
    Add startup and error noise
    Code cleanup
    Fix Bluetooth Blink
2025-01-25 Clean up LED timers
2025-01-27 Add delay to error sound
    Adding delay allows 2 tones to play as intended.
2025-01-27 Add UID endpoint to User Guide.
2025-01-27 Update LipSync_Firmware.ino
    calibTimer -> calibrationTimer
2025-01-27 Separate i2c and cable error pages; sounds tweaks
2025-01-27 Fixed LED blink bug
    Fixed LED blink bug due to timer indexing
2025-01-28 Update LipSync_Firmware.ino
    Move checkI2C to fix bug where display error shows even if display is connected
2025-01-29 Fixed indexing to timers
2025-01-30 Revert "Merge branch 'v4.1' of https://github.com/makersmakingchange/LipSync into v4.1"
    This reverts commit 536cf0e1ade82a7fd4b177d2e41b989ecbaa006a, reversing
    changes made to b2dbd8cf2295ccd9695e6b35d8d2b1d37974bc6b.
2025-01-31 Update LSScreen.h
    Added check at the end of a full calibration to see if menu is active, if so then open menu, if not (such as when a full calibration is initiated through serial) do not open menu
2025-01-31 Update LipSync_User_Guide.docx
    Add Control Hub API endpoint to User Guide.
2025-01-31 Clean-up comments
2025-01-31 Update LSUSB.h
    Missed one g_usbAttempt
2025-02-03 Update LipSync_Firmware.ino
    Fixed full calibration default polarity
2025-02-04 Update LipSync_Firmware.ino
    Rename UBS Retry Connection Function, fix data types in tempDefaultPoint to eliminate compiler warnings. Added delay in startup to allow serial to connect
2025-02-06 Updates
    Global variables renaming
2025-02-06 Add a reset page to screen
    Add a reset page that displays on screen whenever a software reset is called.
2025-02-07 Fixed sip and puff bug
    Fixed bug where sip and puff didn't work initially after powering on. Added 20 ms delay to LSPressure::begin
2025-02-07 Update LSScreen.h
    Added USB_DEBUG warning screen, after the second splash screen.
2025-02-12 Update LSTimer.h
    -Fix interval timer running every loop
    - Add commenting
2025-02-12 Update LSConfig.h
    Clarify action mapping
2025-02-12 Update LSTimer.h
    Add comments for main timer loop
2025-02-12 Update LSTimer.h
    Re-add new timer code.
2025-02-13 Update LSScreen.h
    Updated hardcoded values with named constants
2025-02-14 Fixed bug with timers not incrementing properly
    Moved where timers were being incremented so they would run the correct number of times and then delete the timer. Also reformatted the switch case to a shorter if statement.
2025-02-18 Update LSConfig.h
    Clean up comments
2025-02-19 Update LSTimer.h
    Variable cleanup and commenting
2025-02-22 Fix bug where sip and puff thresholds not loaded from memory properly
    getPressureThreshold doesn't set the sip and puff threshold
2025-02-22 Add ability to disable automatic screen timeout
2025-02-22 Change elapsed() back to millis()
2025-02-22 Remove unused pressure_event member
2025-02-22 Remove unused setThreshold function
2025-02-24 Rename and reorganzie pressure offset measurements functions
    - Add timeouts to pressure offset measurement
    - rename setZeroPressure to updateOffsetPressure
    - change setOffsetPressure to measureOffsetPressure
    - create dediceated setOffsetPressure to access class variable
2025-02-24 Update LSUSB.h
    Cleanup and commenting; add LSUSBGamepad::isConnected()
2025-02-24 Fix offset pressure timeout
2025-02-24 Alternative lastRebootReason method
2025-02-25 Add timeout to USBDEBUG Serial wait
2025-02-25 Add g_lastRebootReason global variable
2025-02-26 Update LipSync_Firmware.ino
    Fix serial print statement
2025-02-28 Added scroll speed menu and adjusted scroll speed
2025-02-28 Update compress_firmware.yml
    Enable firmware compression on each branch.
2025-02-28 Linear scroll levels
2025-02-28 Add call to usbCheckConnection if USB connection times out
2025-03-03 Add CONF_OPERATING_MODE_SAFE
2025-03-03 Seperate (usb)errorCheck from hardwareErrorCheck()
2025-03-03 Modify screens
    Go back to more menu when go back from factory reset, etc.
    Create safe mode menu
    Create timed safe mode screens
2025-03-03 Renamed global variables
2025-03-04 Apply radial deadzone, and linear output starting at 0
    Applies a radial deadzone (inner and outer), and linearizes input from the inner deadzone to the outer deadzone, to output that goes from 0 to the maximum value.
2025-03-04 Update LSJoystick.h
    Removed unused variable
2025-03-04 Properly get resetReason
    Use bootloader function readResetReason as bootloader already reads and clears resetReason
2025-03-04 Update LSScreen.h
    - Clean up error pages
2025-03-05 Longer cable error screen
    Longer cable error screen to give time to read the longer message
2025-03-05 Update LipSync_Firmware.ino
    Remove USB_DEBUG requirement for Safe Mode message serial warnings.
2025-03-05 Update LSAPI.ino
    Use light brightness variable in API instead of hardcoded variable
2025-03-06 Added light brightness into menu and fixed brightness level to output equation
    - Also added a blink after changing the brightness so you can see how bright it is
2025-03-06 Update LSConfig.h
    Fixed bug where mode LED did not light up after closing menu
2025-03-06 Use Inner Deadzone and Outer Deadzone (IZ / OZ)
2025-03-06 Remove applyDeadzone
2025-03-06 Improve LSJoystick readability
2025-03-06 Inner and Outer
2025-03-07 Improve readibility of setouterDeadzone
2025-03-07 Maintian high resolution output from joystick class
2025-03-07 Update LSConfig.h
    update default deadzone values
2025-03-07 Add magnitude and angle to scaleOutput
2025-03-07 Update LipSync_Firmware.ino
    Remove print statement
2025-03-07 Fix deadzonedPointMagnitude and add rounding to pointIntFromMagnitudeAngle
2025-03-14 Fixed text scroll bug for menus longer than 4 lines
2025-03-14 Update LSOutput.h
    Comment out serial print line
2025-03-14 Remove printToSerial functions
2025-03-14 Update Hub files with reinforced screw bosses
    Ribs were added to screw bosses in the Hub to add additional strength
2025-03-14 Remove setLedBrightness serial print
2025-03-17 Disable inputs (buttons, switches, or sip and puff) during full calibration
2025-03-18 Added serial waiting screen
2025-03-18 Update LSPressure.h
    Add linebreak to pressure sensor timeout error message
2025-03-19 Fixed menu indexing for cursor and scroll
2025-03-20 Remove too long error message
2025-03-20 Update LipSync_Firmware.ino
    Add watchdog case for safe mode reason
2025-03-21 Update LipSync_Firmware.ino
    Fixed missing bracket
2025-03-24 Turn off USB DEBUG
2025-03-27 Adjust default inner deadzone
2025-03-27 Minor typo correction
2025-03-28 Update LSMemory.h
    Catch deserialization error
2025-03-29 Add info page to more menu
2025-03-29 Remove Pressure Mode
2025-04-01 Add updated documentation
2025-04-01 Update LipSync-4.jpg
    Update with newer photo showing new mouthpiece.
2025-04-02 Update LipSync Firmware Update Guide
2025-04-10 Add Update About MMC GitHub Action
2025-06-10 Add message on cable availability.
    Changed readme to reflect no stock on DigiKey cable component
2025-07-21 Update README.md
    Add more descriptive alt text
2025-07-29 Create TLV493D-A1B6.zip
    Add copy of deprecated library
2025-08-07 Rename OKH-LipSync.yml to okh-LipSync.yml
    Match OKH specification
2026-01-05 Update links in okh-LipSync.yml to use 'main' branch
2026-01-17 Added troubleshooting for Mac
    Added troubleshooting steps for Python on Mac on Derrick's behalf since he doesn't have write access to this repository
2026-01-21 Updated licensing information
    Updated licenses on the open source hardware parts used in LipSync and fixed spelling of one of the contributors name
